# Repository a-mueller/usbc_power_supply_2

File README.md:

# USB C POWER SUPPLY 2 (Single Cell LiPo 18650)

I made this as I couldn't find any board that did exactly what I needed. I used some of these (https://www.ebay.co.uk/itm/196094318206) before, but they have two main issues:

1) Doesn't charge with most USB chargers, as they ignore PD and only charge with USB-A to USB-C cables
2) Don't switch between battery and usb power

## Warning

This board does protect against overcharging, but not against discharge, so make sure you use protected cells.

## Schematic

[Schematic](img/schematic.png)

## PCB

## Parts

<table>
    <tr><td>J1</td><td><a href="https://uk.farnell.com/global-connector-technology/usb4125-gf-a-0190/usb-conn-type-c-r-a-rcpt-6pos/dp/3777661">GCT USB4125-GF-A-0190</a></td></tr>
    <tr><td>R2,R3</td><td><a href="https://uk.farnell.com/panasonic/erj6geyj512v/res-5k1-5-0-125w-0805-thick-film/dp/2057715">PANASONIC ERJ6GEYJ512V</a></td></tr>
    <tr><td>R4,R5,R7</td><td><a href="https://uk.farnell.com/panasonic/erj3geyj471v/res-470r-5-0-1w-0603-thick-film/dp/2059592">PANASONIC ERJ3GEYJ471V</a></td></tr>
    <tr><td>D1,D2,D3</td><td><a href="https://uk.farnell.com/multicomp-pro/mp008284/led-blue-200mcd-475nm-0603/dp/3796315">MULTICOMP PRO MP008284 (D1->Green, D2-> Blue, D3-> Red)</a></td></tr>
    <tr><td>R6</td><td><a href="https://uk.farnell.com/panasonic/erjup3j102v/res-1k-5-0-25w-0603/dp/3579508">PANASONIC ERJUP3J102V</a></td></tr>
    <tr><td>U2</td><td><a href="https://uk.farnell.com/microchip/mcp73833-ami-mf/batt-charger-li-ion-pol-1a-dfn/dp/2709765">MICROCHIP MCP73833-AMI/MF</a></td></tr>
    <tr><td>C1,C2,C3</td><td><a href="https://uk.farnell.com/kemet/c0805c106k8pactu/cap-10-f-10v-10-x5r-0805/dp/1463362">KEMET C0805C106K8PACTU</a></td></tr>
    <tr><td>U1</td><td><a href="https://uk.farnell.com/on-semiconductor/mbr0540t3g/diode-schottky-0-5a-40v-sod-123/dp/2101839">ONSEMI MBR0540T3G (500mA) or PMEG3010EGW (1A)</a></td></tr>
    <tr><td>Q1</td><td><a href="https://uk.farnell.com/diodes-inc/dmg3415ufy4q-7/mosfet-p-ch-16v-2-5a-x2-dfn2015/dp/3943489">DIODES INC. DMG3415UFY4Q-7</a></td></tr>
    <tr><td>R1,R8</td><td><a href="https://uk.farnell.com/panasonic/erj3geyj103v/res-10k-5-0-1w-0603-thick-film/dp/2059627">PANASONIC ERJ3GEYJ103V</a></td></tr>
    <tr><td>J2,J3</td><td>JST PH 2mm connectors</td></tr>

</table>

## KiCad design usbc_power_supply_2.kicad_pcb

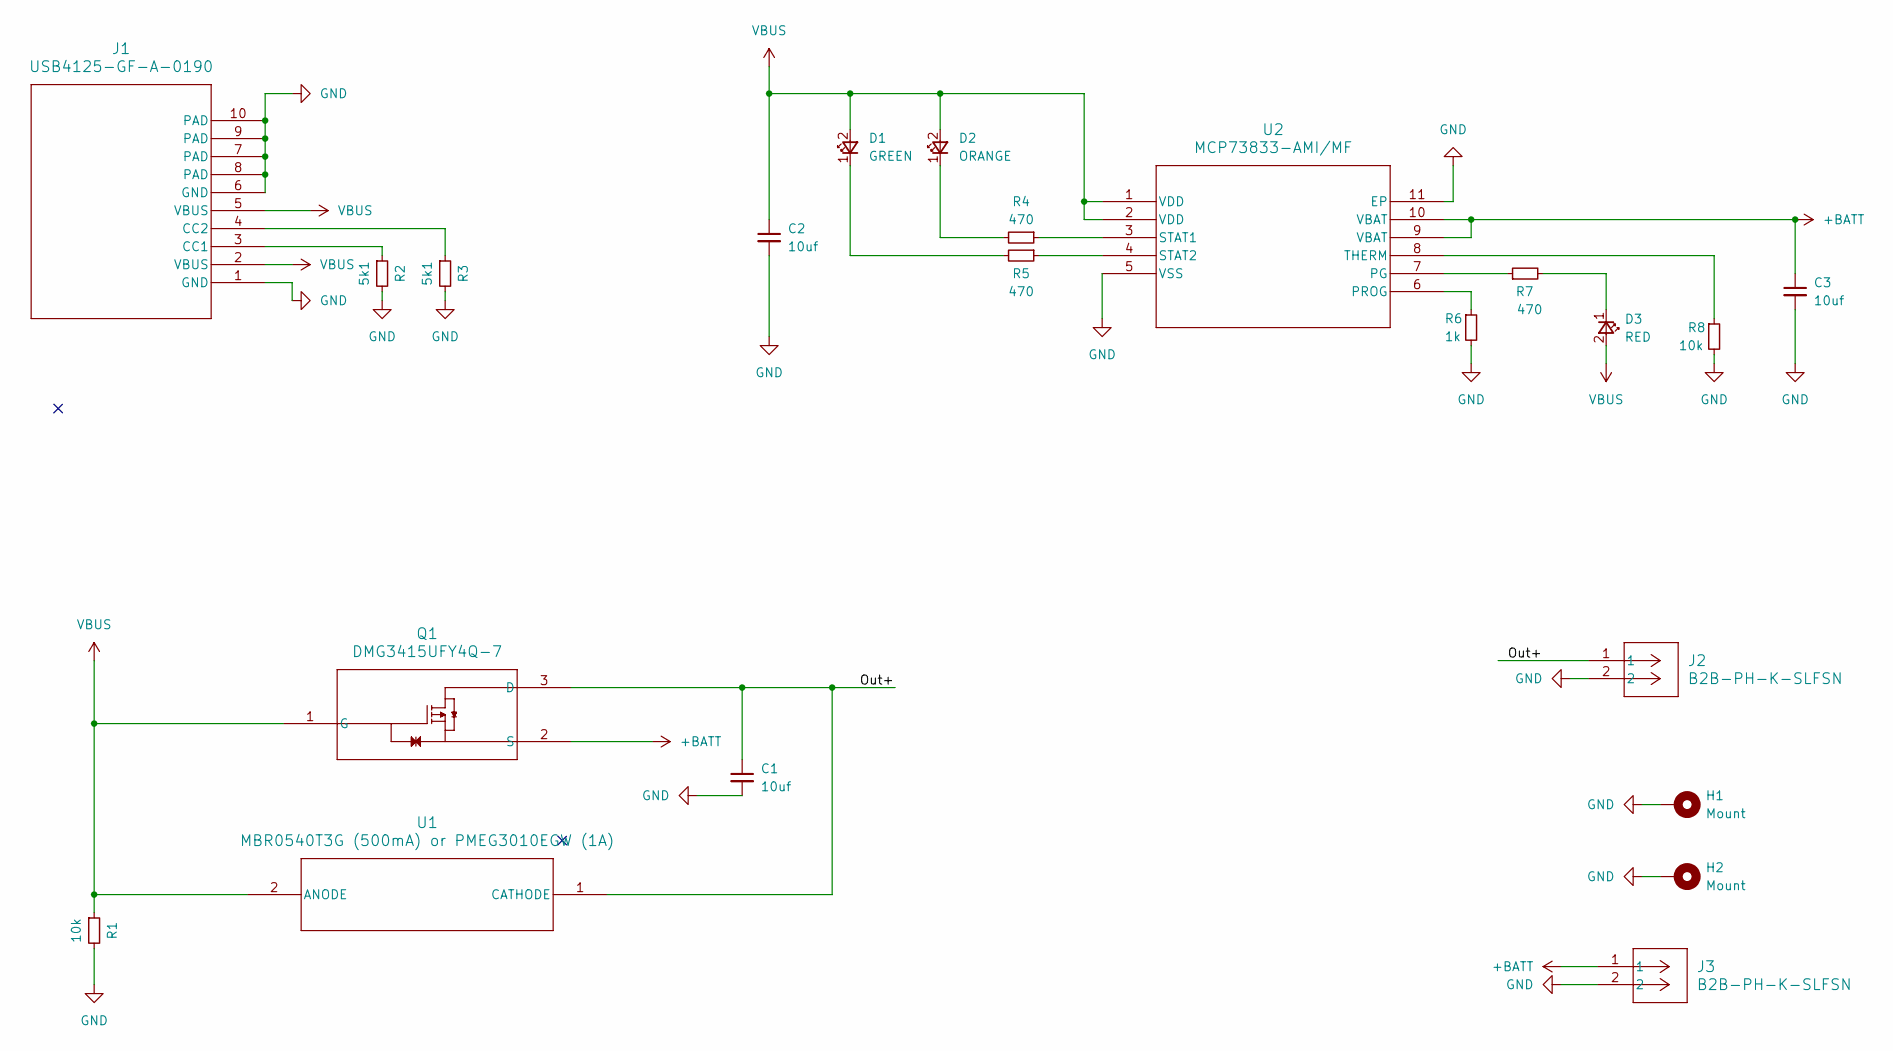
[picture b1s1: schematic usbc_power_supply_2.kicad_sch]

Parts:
C1, C2, C3: 10uf; C0805
D1: GREEN; Multicomp_SMD_LED_0603
D2: ORANGE; Multicomp_SMD_LED_0603
D3: RED; Multicomp_SMD_LED_0603
H1, H2: Mount; MountingHole_2.2mm_M2_Pad
J1: USB4125-GF-A-0190; CONN6_125-GF-A-0190_GCT
J2, J3: B2B-PH-K-SLFSN; CONN_B2B-PH-K-SLFSN_JST
Q1: DMG3415UFY4Q-7; TRANS_DMG3415UFY4Q-7_DIO
R1, R8: 10k; ERJ3G_PAN
R2, R3: 5k1; ERJ6G_PAN
R4, R5, R7: 470; ERJ3G_PAN
R6: 1k; ERJUP3_PAN
U1: MBR0540T3G (500mA) or PMEG3010EGW (1A); SOD-123_ONS
U2: MCP73833-AMI/MF; DFN10_3x3MC_MCH

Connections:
+BATT: C3.1, J3.1, Q1.2 (S), U2.9 (VBAT), U2.10 (VBAT)
/Out+: C1.1, J2.1, Q1.3 (D), U1.1 (CATHODE)
GND: C1.2, C2.2, C3.2, H1.1, H2.1, J1.1 (GND), J1.6 (GND), J1.7 (PAD), J1.8 (PAD), J1.9 (PAD), J1.10 (PAD), J2.2, J3.2, R1.2, R2.2, R3.2, R6.2, R8.2, U2.5 (VSS), U2.11 (EP)
unnamed: D1.1 (K), R5.2
unnamed: D2.1 (K), R4.2
unnamed: D3.1 (K), R7.2
unnamed: J1.3 (CC1), R2.1
unnamed: J1.4 (CC2), R3.1
unnamed: R7.1, U2.7 (PG)
unnamed: R6.1, U2.6 (PROG)
unnamed: R4.1, U2.3 (STAT1)
unnamed: R5.1, U2.4 (STAT2)
unnamed: R8.1, U2.8 (THERM)
VBUS: C2.1, D1.2 (A), D2.2 (A), D3.2 (A), J1.2 (VBUS), J1.5 (VBUS), Q1.1 (G), R1.1, U1.2 (ANODE), U2.1 (VDD), U2.2 (VDD)

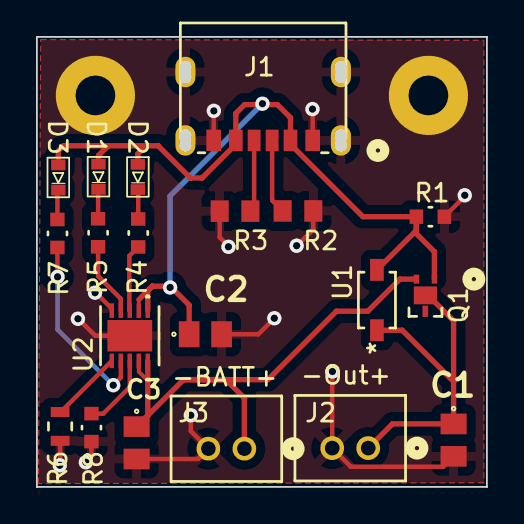
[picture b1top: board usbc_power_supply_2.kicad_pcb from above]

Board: 2 copper layers, 24.5 x 24.5 mm, 22 parts (0 on the bottom side), 14 nets.

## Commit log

2024-02-18 Initial Commint
2024-02-18 adds more documentation
2024-02-29 updates mounting holes with pads, optional 1A shottkyx
2024-04-23 upgrades board files to kicad
